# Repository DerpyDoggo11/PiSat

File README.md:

# PiSat
A GPS Microcontroller for RTK GPS applications

## 3D Preview

## Wiring

## Schematic

### Download the ./latestProduction folder to begin fabricating through JLCPCB. 

## Introduction
PiSat is a complete microcontroller with an embbedded GPS chip all in the footprint of a Raspbbery Pi. It uses an RP2350 for parallel computing + an esp32 for wifi connectivity. In addition, it uses the PNT-SG3FS-TR GPS chip with an SMA connector to attach an external GPS antenna. It also can run completely on battery power for an estimated 12 hours (based on the suggested battery) at full load.

The main use case for this is in the Real Time Kinematic (RTK) GPS system, which requires two GPS recievers: one at a known location and one at the location being tracked. By calculating the error that both recievers share with other satilletes, this method can track an object down to just a few centimeters. The main drawback to RTK GPS systems is that they usually require expensive mcu for the calculations + external GPS modules which can increase the cost substantially. A fully embbedded approach makes the price much more approachable to hobbists.

Note: this is licensed under the GPL/GNU license which means editing it is fine, just make sure to keep it open source.

## Bill of Materials 

### (Minimum build for RTK GPS system: 2 PiSats)

| Quantity | Components |  Price | Link |
|--------- |----------|----------| -----|
| 2  | 18650 Batteries | ~$20 (with shipping) | [here](https://liionwholesale.com/products/molicel-npe-inr-18650-m35a-10a-3500mah-flat-top-18650-battery-authorized-distributor?variant=32004772528197)
| 2 | GPS Antenna | $7 (Flexible Antenna) or $10 (Straight Antenna) | [here](https://www.aliexpress.us/item/3256804609969855.html?spm=a2g0o.productlist.main.22.2d61135313537Z&algo_pvid=a8f1f363-3e79-462c-8226-c544dbba9469&algo_exp_id=a8f1f363-3e79-462c-8226-c544dbba9469-21&pdp_ext_f=%7B%22order%22%3A%221213%22%2C%22eval%22%3A%221%22%2C%22fromPage%22%3A%22search%22%7D&pdp_npi=6%40dis%21USD%215.00%213.50%21%21%215.00%213.50%21%402103119c17817420491787632e4325%2112000030518552990%21sea%21US%217493938711%21X%211%210%21n_tag%3A-29913%3Bd%3Ad260408f%3Bm03_new_user%3A-29895&curPageLogUid=FQzx1wWXtUoX&utparam-url=scene%3Asearch%7Cquery_from%3A%7Cx_object_id%3A1005004796284607%7C_p_origin_prod%3A#nav-specification) or [here](https://www.aliexpress.us/item/3256809038076860.html?spm=a2g0o.productlist.main.2.2151p6Ftp6FtTh&algo_pvid=996be7bb-70aa-4be7-8faf-292b35948f71&algo_exp_id=996be7bb-70aa-4be7-8faf-292b35948f71-1&pdp_ext_f=%7B%22order%22%3A%22245%22%2C%22eval%22%3A%221%22%2C%22fromPage%22%3A%22search%22%7D&pdp_npi=6%40dis%21USD%2113.26%215.19%21%21%2189.21%2134.92%21%402101e80317817623348108445eaaa5%2112000048375428405%21sea%21US%217493938711%21X%211%210%21n_tag%3A-29913%3Bd%3Ad260408f%3Bm03_new_user%3A-29895%3BpisId%3A5000000209191311&curPageLogUid=Bw3eYI7vcVpx&utparam-url=scene%3Asearch%7Cquery_from%3A%7Cx_object_id%3A1005009224391612%7C_p_origin_prod%3A#nav-specification)
| 2 | 2.4G Wifi Antenna | $3.55 | [here](https://www.aliexpress.us/item/3256802833801038.html?spm=a2g0o.productlist.main.17.44bbCrBdCrBdFl&algo_pvid=20d56933-2b0c-45d5-8601-1bc6a9682401&algo_exp_id=20d56933-2b0c-45d5-8601-1bc6a9682401-16&pdp_ext_f=%7B%22order%22%3A%221074%22%2C%22eval%22%3A%221%22%2C%22fromPage%22%3A%22search%22%7D&pdp_npi=6%40dis%21USD%213.55%213.52%21%21%213.55%213.52%21%402101ef5e17781321493642302e40a6%2112000023272348781%21sea%21US%217493938711%21X%211%210%21n_tag%3A-29913%3Bd%3A21b1ce8d%3Bm03_new_user%3A-29895&curPageLogUid=rLnZuf4b98Bi&utparam-url=scene%3Asearch%7Cquery_from%3A%7Cx_object_id%3A1005003020115790%7C_p_origin_prod%3A)
| 2  | PiSat PCBs | ~$100 (with shipping, cost can vary widely however) | Download repo, extract fabrication files from ./latestProduction, and fabricate through JLCPCB (complete instructions for this may come soon)

Total cost: **$130.55**

Cost per unit: **$65.28**

----

## Tools:
- Soldering iron + solder

## Assembly:
1. (If using vertical mount case) Screw into 3 of the mounting holes on the board, only screw into the 1 mounting hole below the battery if completely necessary
2. Solder on the battery connector
3. Screw in the wifi antenna onto the esp32
4. Screw in the GPS antenna onto the SMA connector
5. Insert battery into battery connector and turn on

## Demonstration Video
https://www.youtube.com/watch?v=5pDu0XT5UDQ

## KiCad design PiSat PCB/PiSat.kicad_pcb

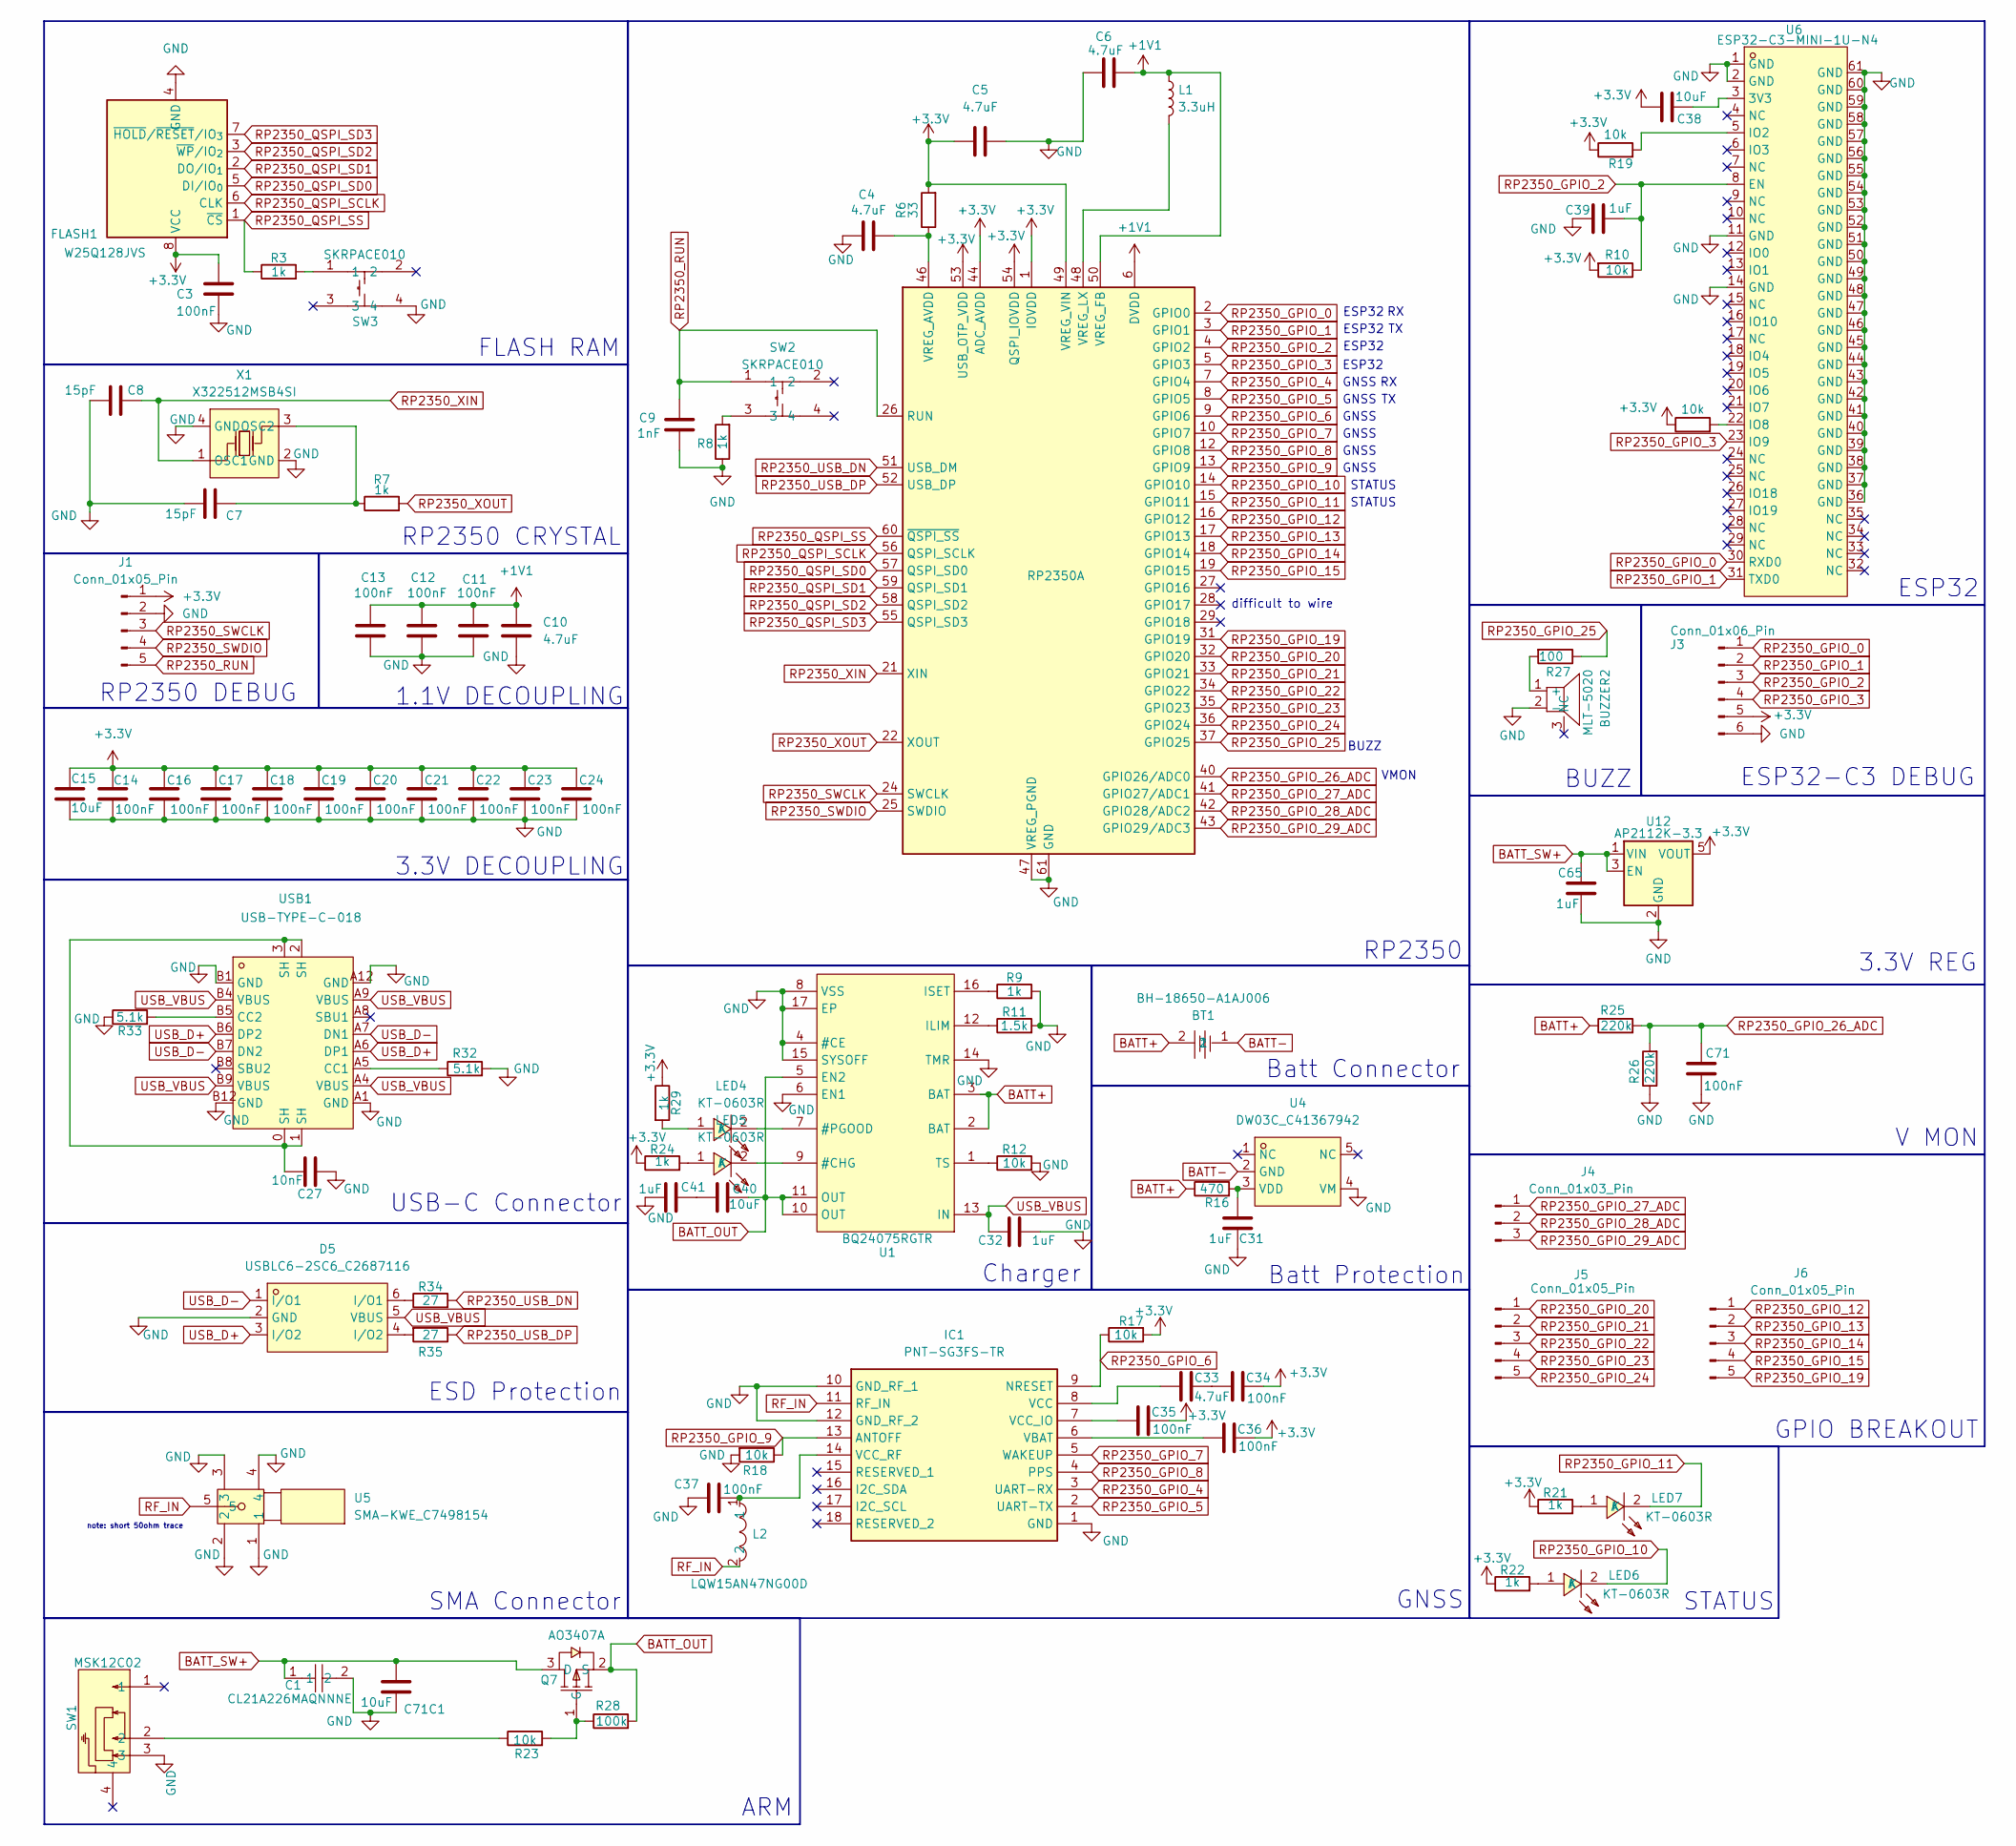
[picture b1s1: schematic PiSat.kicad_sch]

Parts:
BT1: BH-18650-A1AJ006; BAT-TH_BH-18650-A1AJ006; MPN BH-18650-A1AJ006; LCSC Part C5290175
BUZZER2: MLT-5020; BUZ-SMD_L5.0-W5.5-P4.60; MPN MLT-5020; LCSC Part C94598
C1: CL21A226MAQNNNE; C0805; MPN CL21A226MAQNNNE; LCSC Part C45783
C3, C11, C12, C13, C14, C16, C17, C18, C19, C20, C21, C22, C23, C24, C34, C35, C36, C37, C71: 100nF; C_0603_1608Metric
C4, C5, C6, C10, C33: 4.7uF; C_0603_1608Metric
C7, C8: 15pF; C_0603_1608Metric
C9: 1nF; C_0603_1608Metric
C15, C71C1: 10uF; C_0805_2012Metric
C27: 10nF; C_0603_1608Metric
C31, C32, C39, C41, C65: 1uF; C_0603_1608Metric
C38, C40: 10uF; C_0603_1608Metric
D5: USBLC6-2SC6_C2687116; SOT-23-6_L2.9-W1.6-P0.95-LS2.8-BL; MPN USBLC6-2SC6; LCSC Part C2687116
FLASH1: W25Q128JVS; SOIC-8_5.3x5.3mm_P1.27mm
IC1: PNT-SG3FS-TR; PNTSG3FSTR; Manufacturer_Part_Number PNT-SG3FS-TR
J1, J5, J6: Conn_01x05_Pin; PinHeader_1x05_P2.54mm_Vertical
J3: Conn_01x06_Pin; PinHeader_1x06_P2.54mm_Vertical
J4: Conn_01x03_Pin; PinHeader_1x03_P2.54mm_Vertical
L1: 3.3uH; L_1210_3225Metric
L2: LQW15AN47NG00D; L0402; MPN LQW15AN47NG00D; LCSC Part C22334
LED4, LED5, LED6, LED7: KT-0603R; LED-SMD_L1.6-W0.8-R-RD; MPN KT-0603R; LCSC Part C2286
Q7: AO3407A; SOT-23-3_L2.9-W1.6-P1.90-LS2.8-BR; MPN AO3407A; LCSC Part C15155
R3, R7, R8, R9, R21, R22, R24, R29: 1k; R_0603_1608Metric
R6: 33; R_0603_1608Metric
R10, R12, R17, R18, R19, R20, R23: 10k; R_0603_1608Metric
R11: 1.5k; R_0603_1608Metric
R16: 470; R_0603_1608Metric
R25, R26: 220k; R_0603_1608Metric
R27: 100; R_0603_1608Metric
R28: 100k; R_0603_1608Metric
R32, R33: 5.1k; R_0603_1608Metric
R34, R35: 27; R_0603_1608Metric
RP2350: RP2350A; QFN-60-1EP_7x7mm_P0.4mm_EP3.4x3.4mm
SW1: MSK12C02; SW-TH_MSK12C02; MPN MSK12C02; LCSC Part C431540
SW2, SW3: SKRPACE010; KEY-SMD_4P-L4.2-W3.2-P2.20-LS4.6; MPN SKRPACE010; LCSC Part C139797
U1: BQ24075RGTR; QFN-16_L3.0-W3.0-P0.50-TL-EP1.7; MPN BQ24075RGTR; LCSC Part C15464
U4: DW03C_C41367942; SOT-23-5_L2.9-W1.6-P0.95-LS2.9-BL; MPN DW03C; LCSC Part C41367942
U5: SMA-KWE_C7498154; SMA-TH_SMA-KWE_C7498154; MPN SMA-KWE; LCSC Part C7498154
U6: ESP32-C3-MINI-1U-N4; WIFIM-SMD_61P-L13.2-W12.5-P0.80; MPN ESP32-C3-MINI-1U-N4; LCSC Part C2911374
U12: AP2112K-3.3; SOT-23-5
USB1: USB-TYPE-C-018; USB-C_SMD-TYPE-C-31-M-12; MPN USB-TYPE-C-018; LCSC Part C2927038
X1: X322512MSB4SI; CRYSTAL-SMD_4P-L3.2-W2.5-BL; MPN X322512MSB4SI; LCSC Part C9002

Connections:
+1V1: C6.2, C10.1, C11.1, C12.1, C13.1, L1.1, RP2350.6 (DVDD), RP2350.23 (DVDD), RP2350.39 (DVDD), RP2350.50 (VREG_FB)
+3.3V: C3.1, C5.1, C14.1, C15.1, C16.1, C17.1, C18.1, C19.1, C20.1, C21.1, C22.1, C23.1, C24.1, C34.2, C35.2, C36.2, C38.2, FLASH1.8 (VCC), J1.1, J3.5, R6.2, R10.2, R17.2, R19.1, R20.1, R21.1, R22.1, R24.1, R29.1, RP2350.1 (IOVDD), RP2350.11 (IOVDD), RP2350.20 (IOVDD), RP2350.30 (IOVDD), RP2350.38 (IOVDD), RP2350.44 (ADC_AVDD), RP2350.45 (IOVDD), RP2350.49 (VREG_VIN), RP2350.53 (USB_OTP_VDD), RP2350.54 (QSPI_IOVDD), U12.5 (VOUT)
BATT+: BT1.2, R16.1, R25.1, U1.2 (BAT), U1.3 (BAT)
BATT-: BT1.1, U4.2 (GND)
BATT_OUT: C40.1, Q7.2 (S), R28.2, U1.5 (EN2), U1.10 (OUT), U1.11 (OUT)
BATT_SW+: C1.1, C65.2, C71C1.2, Q7.3 (D), U12.1 (VIN), U12.3 (EN)
GND: BUZZER2.2 (-), C1.2, C3.2, C4.1, C5.2, C6.1, C7.1, C8.1, C9.2, C10.2, C11.2, C12.2, C13.2, C14.2, C15.2, C16.2, C17.2, C18.2, C19.2, C20.2, C21.2, C22.2, C23.2, C24.2, C27.1, C31.2, C32.1, C37.1, C39.1, C41.1, C65.1, C71.1, C71C1.1, D5.2 (GND), FLASH1.4 (GND), IC1.1 (GND), IC1.10 (GND_RF_1), IC1.12 (GND_RF_2), J1.2, J3.6, R8.1, R9.2, R11.2, R12.2, R18.2, R26.1, R32.2, R33.1, RP2350.47 (VREG_PGND), RP2350.61 (GND), SW1.3, SW3.4, U1.4 (#CE), U1.6 (EN1), U1.8 (VSS), U1.14 (TMR), U1.15 (SYSOFF), U1.17 (EP), U4.4 (VM), U5.1, U5.2, U5.3, U5.4, U6.1 (GND), U6.2 (GND), U6.11 (GND), U6.14 (GND), U6.36 (GND), U6.37 (GND), U6.38 (GND), U6.39 (GND), U6.40 (GND), U6.41 (GND), U6.42 (GND), U6.43 (GND), U6.44 (GND), U6.45 (GND), U6.46 (GND), U6.47 (GND), U6.48 (GND), U6.49 (GND), U6.50 (GND), U6.51 (GND), U6.52 (GND), U6.53 (GND), U6.54 (GND), U6.55 (GND), U6.56 (GND), U6.57 (GND), U6.58 (GND), U6.59 (GND), U6.60 (GND), U6.61 (GND), U12.2 (GND), USB1.A1 (GND), USB1.A12 (GND), USB1.B1 (GND), USB1.B12 (GND), X1.2 (GND), X1.4 (GND)
unnamed: BUZZER2.1 (+), R27.2
unnamed: C27.2, USB1.0 (SH), USB1.1 (SH), USB1.2 (SH), USB1.3 (SH)
unnamed: C33.2, C34.1
unnamed: C40.2, C41.2
unnamed: D5.6 (I/O1), R34.1
unnamed: D5.4 (I/O2), R35.2
unnamed: C36.1, IC1.6 (VBAT)
unnamed: C33.1, IC1.8 (VCC)
unnamed: C35.1, IC1.7 (VCC_IO)
unnamed: C37.2, IC1.14 (VCC_RF), L2.1
unnamed: LED4.1 (A), R29.2
unnamed: LED4.2 (K), U1.7 (#PGOOD)
unnamed: LED5.1 (A), R24.2
unnamed: LED5.2 (K), U1.9 (#CHG)
unnamed: LED6.1 (A), R22.2
unnamed: LED7.1 (A), R21.2
unnamed: Q7.1 (G), R23.2, R28.1
unnamed: R3.2, SW3.1
unnamed: R8.2, SW2.3
unnamed: R23.1, SW1.2
unnamed: C4.2, R6.1, RP2350.46 (VREG_AVDD)
unnamed: L1.2, RP2350.48 (VREG_LX)
unnamed: R11.1, U1.12 (ILIM)
unnamed: R9.1, U1.16 (ISET)
unnamed: R12.1, U1.1 (TS)
unnamed: C31.1, R16.2, U4.3 (VDD)
unnamed: C38.1, U6.3 (3V3)
unnamed: R19.2, U6.5 (IO2)
unnamed: R20.2, U6.22 (IO8)
unnamed: R32.1, USB1.A5 (CC1)
unnamed: R33.2, USB1.B5 (CC2)
unnamed: C7.2, R7.1, X1.3 (OSC2)
RF_IN: IC1.11 (RF_IN), L2.2, U5.5
RP2350_GPIO_0: J3.1, RP2350.2 (GPIO0), U6.30 (RXD0)
RP2350_GPIO_1: J3.2, RP2350.3 (GPIO1), U6.31 (TXD0)
RP2350_GPIO_2: C39.2, J3.3, R10.1, RP2350.4 (GPIO2), U6.8 (EN)
RP2350_GPIO_3: J3.4, RP2350.5 (GPIO3), U6.23 (IO9)
RP2350_GPIO_4: IC1.3 (UART-RX), RP2350.7 (GPIO4)
RP2350_GPIO_5: IC1.2 (UART-TX), RP2350.8 (GPIO5)
RP2350_GPIO_6: IC1.9 (NRESET), R17.1, RP2350.9 (GPIO6)
RP2350_GPIO_7: IC1.5 (WAKEUP), RP2350.10 (GPIO7)
RP2350_GPIO_8: IC1.4 (PPS), RP2350.12 (GPIO8)
RP2350_GPIO_9: IC1.13 (ANTOFF), R18.1, RP2350.13 (GPIO9)
RP2350_GPIO_10: LED6.2 (K), RP2350.14 (GPIO10)
RP2350_GPIO_11: LED7.2 (K), RP2350.15 (GPIO11)
RP2350_GPIO_12: J6.1, RP2350.16 (GPIO12)
RP2350_GPIO_13: J6.2, RP2350.17 (GPIO13)
RP2350_GPIO_14: J6.3, RP2350.18 (GPIO14)
RP2350_GPIO_15: J6.4, RP2350.19 (GPIO15)
RP2350_GPIO_19: J6.5, RP2350.31 (GPIO19)
RP2350_GPIO_20: J5.1, RP2350.32 (GPIO20)
RP2350_GPIO_21: J5.2, RP2350.33 (GPIO21)
RP2350_GPIO_22: J5.3, RP2350.34 (GPIO22)
RP2350_GPIO_23: J5.4, RP2350.35 (GPIO23)
RP2350_GPIO_24: J5.5, RP2350.36 (GPIO24)
RP2350_GPIO_25: R27.1, RP2350.37 (GPIO25)
RP2350_GPIO_26_ADC: C71.2, R25.2, R26.2, RP2350.40 (GPIO26/ADC0)
RP2350_GPIO_27_ADC: J4.1, RP2350.41 (GPIO27/ADC1)
RP2350_GPIO_28_ADC: J4.2, RP2350.42 (GPIO28/ADC2)
RP2350_GPIO_29_ADC: J4.3, RP2350.43 (GPIO29/ADC3)
RP2350_QSPI_SCLK: FLASH1.6 (CLK), RP2350.56 (QSPI_SCLK)
RP2350_QSPI_SD0: FLASH1.5 (DI/IO_{0}), RP2350.57 (QSPI_SD0)
RP2350_QSPI_SD1: FLASH1.2 (DO/IO_{1}), RP2350.59 (QSPI_SD1)
RP2350_QSPI_SD2: FLASH1.3 (~WP/IO_{2}), RP2350.58 (QSPI_SD2)
RP2350_QSPI_SD3: FLASH1.7 (~HOLD/~RESET/IO_{3}), RP2350.55 (QSPI_SD3)
RP2350_QSPI_SS: FLASH1.1 (~CS), R3.1, RP2350.60 (~QSPI_SS)
RP2350_RUN: C9.1, J1.5, RP2350.26 (RUN), SW2.1
RP2350_SWCLK: J1.3, RP2350.24 (SWCLK)
RP2350_SWDIO: J1.4, RP2350.25 (SWDIO)
RP2350_USB_DN: R34.2, RP2350.51 (USB_DM)
RP2350_USB_DP: R35.1, RP2350.52 (USB_DP)
RP2350_XIN: C8.2, RP2350.21 (XIN), X1.1 (OSC1)
RP2350_XOUT: R7.2, RP2350.22 (XOUT)
USB_D+: D5.3 (I/O2), USB1.A6 (DP1), USB1.B6 (DP2)
USB_D-: D5.1 (I/O1), USB1.A7 (DN1), USB1.B7 (DN2)
USB_VBUS: C32.2, D5.5 (VBUS), U1.13 (IN), USB1.A4 (VBUS), USB1.A9 (VBUS), USB1.B4 (VBUS), USB1.B9 (VBUS)

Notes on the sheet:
GNSS
FLASH RAM
V MON
note: short 50ohm trace
ESP32-C3 DEBUG
Batt Protection
STATUS
RP2350 CRYSTAL
ESP32
ARM
BUZZ
ESD Protection
difficult to wire
SMA Connector
GPIO BREAKOUT
Charger
VMON
RP2350
3.3V DECOUPLING
3.3V REG
USB-C Connector
RP2350 DEBUG
Batt Connector
1.1V DECOUPLING

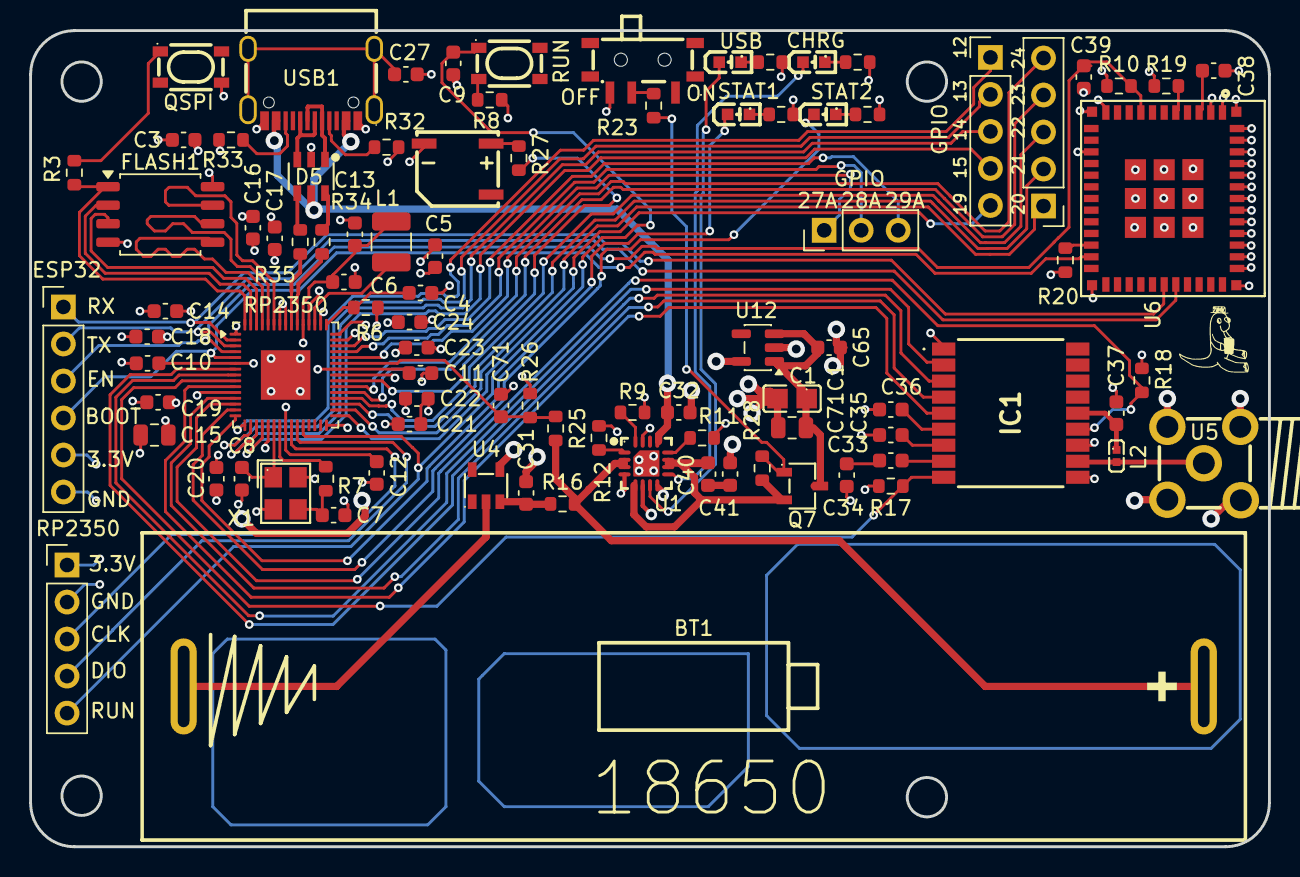
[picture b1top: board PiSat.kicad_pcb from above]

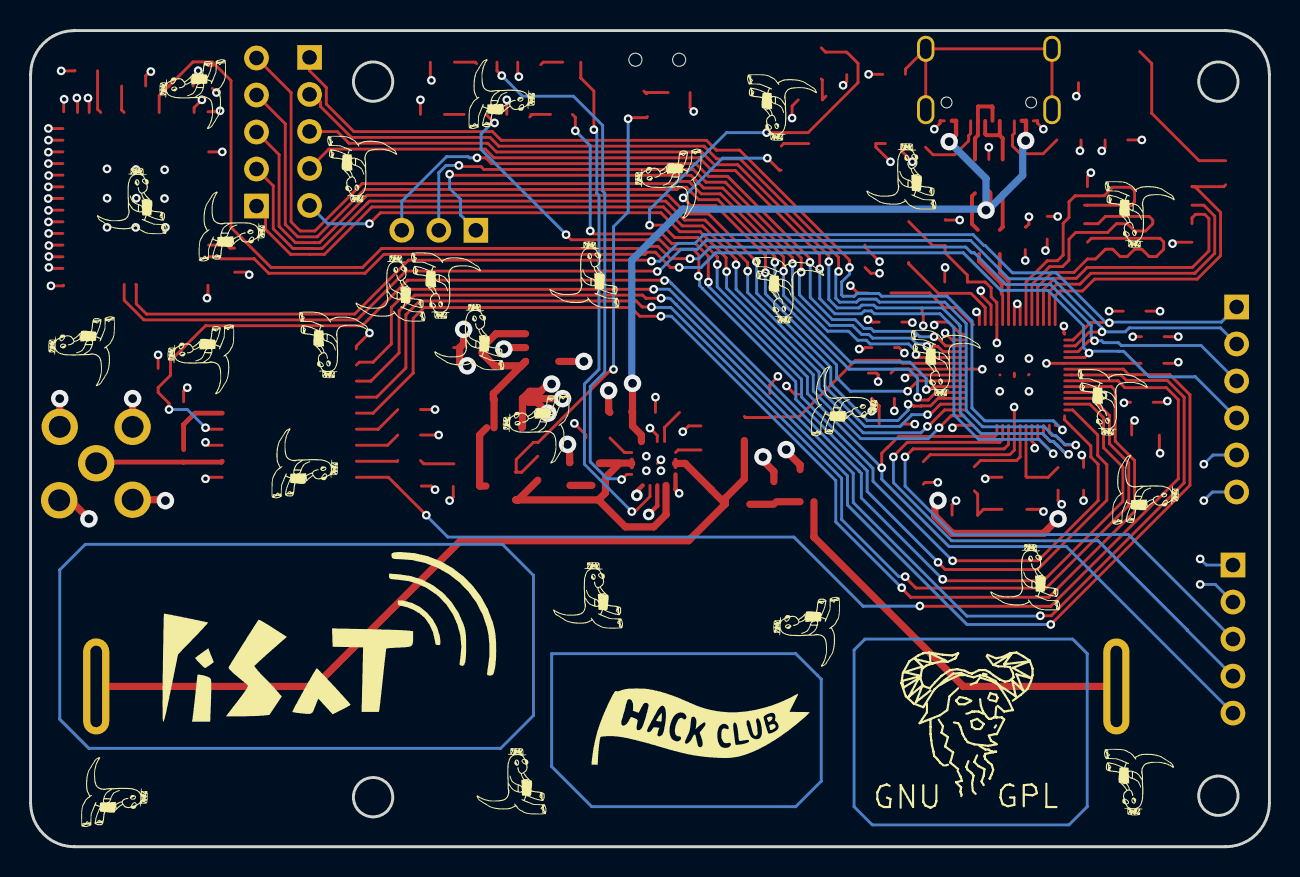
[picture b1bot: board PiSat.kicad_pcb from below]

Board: 4 copper layers, 85.0 x 56.0 mm, 94 parts (2 on the bottom side), 83 nets.

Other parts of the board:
GNU: Symbol_GNU-Logo_SilkscreenTop
hackclub: LOGO; hackclub

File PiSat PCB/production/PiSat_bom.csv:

Designator,Footprint,Quantity,Value,LCSC Part #
BT1,BAT-TH_BH-18650-A1AJ006,1,BH-18650-A1AJ006,C5290175
BUZZER2,BUZ-SMD_L5.0-W5.5-P4.60,1,MLT-5020,C94598
C1,C0805,1,CL21A226MAQNNNE,C45783
"C10, C33, C4, C5, C6",0603,5,4.7uF,
"C11, C12, C13, C14, C16, C17, C18, C19, C20, C21, C22, C23, C24, C3, C34, C35, C36, C37, C71",0603,19,100nF,
"C15, C71C1",0805,2,10uF,
C27,0603,1,10nF,
"C31, C32, C39, C41, C65",0603,5,1uF,
"C38, C40",0603,2,10uF,
"C7, C8",0603,2,15pF,
C9,0603,1,1nF,
D5,SOT-23-6_L2.9-W1.6-P0.95-LS2.8-BL,1,USBLC6-2SC6_C2687116,C2687116
FLASH1,SOIC-8_5.3x5.3mm_P1.27mm,1,W25Q128JVS,
IC1,PNTSG3FSTR,1,PNT-SG3FS-TR,
"J1, J5, J6",PinHeader_1x05_P2.54mm_Vertical,3,Conn_01x05_Pin,C32713271
J3,PinHeader_1x06_P2.54mm_Vertical,1,Conn_01x06_Pin,C32713272
J4,PinHeader_1x03_P2.54mm_Vertical,1,Conn_01x03_Pin,C32713269
L1,1210,1,3.3uH,
L2,L0402,1,LQW15AN47NG00D,C22334
"LED4, LED5, LED6, LED7",LED-SMD_L1.6-W0.8-R-RD,4,KT-0603R,C2286
Q7,SOT-23-3_L2.9-W1.6-P1.90-LS2.8-BR,1,AO3407A,C15155
"R10, R12, R17, R18, R19, R20, R23",0603,7,10k ohm,
R11,0603,1,1.5k ohm,
R16,0603,1,470 ohm,
"R21, R22, R24, R29, R3, R7, R8, R9",0603,8,1k ohm,
"R25, R26",0603,2,220k ohm,
R27,0603,1,100 ohm,
R28,0603,1,100k ohm,
"R32, R33",0603,2,5.1k ohm,
"R34, R35",0603,2,27 ohm,
R6,0603,1,33 ohm,
RP2350,QFN-60-1EP_7x7mm_P0.4mm_EP3.4x3.4mm,1,RP2350A,
SW1,SW-TH_MSK12C02,1,MSK12C02,C431540
"SW2, SW3",KEY-SMD_4P-L4.2-W3.2-P2.20-LS4.6,2,SKRPACE010,C139797
U1,QFN-16_L3.0-W3.0-P0.50-TL-EP1.7,1,BQ24075RGTR,C15464
U12,SOT-23-5,1,AP2112K-3.3,
U4,SOT-23-5_L2.9-W1.6-P0.95-LS2.9-BL,1,DW03C_C41367942,C41367942
U5,SMA-TH_SMA-KWE_C7498154,1,SMA-KWE_C7498154,C7498154
U6,WIFIM-SMD_61P-L13.2-W12.5-P0.80,1,ESP32-C3-MINI-1U-N4,C2911374
USB1,USB-C_SMD-TYPE-C-31-M-12,1,USB-TYPE-C-018,C2927038
X1,CRYSTAL-SMD_4P-L3.2-W2.5-BL,1,X322512MSB4SI,C9002

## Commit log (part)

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2026-06-05 sync
2026-06-18 fixed flash ram wiring + added readme
